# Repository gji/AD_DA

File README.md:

AD_DA
=====

AD/DA for Opal Kelly XEM6310

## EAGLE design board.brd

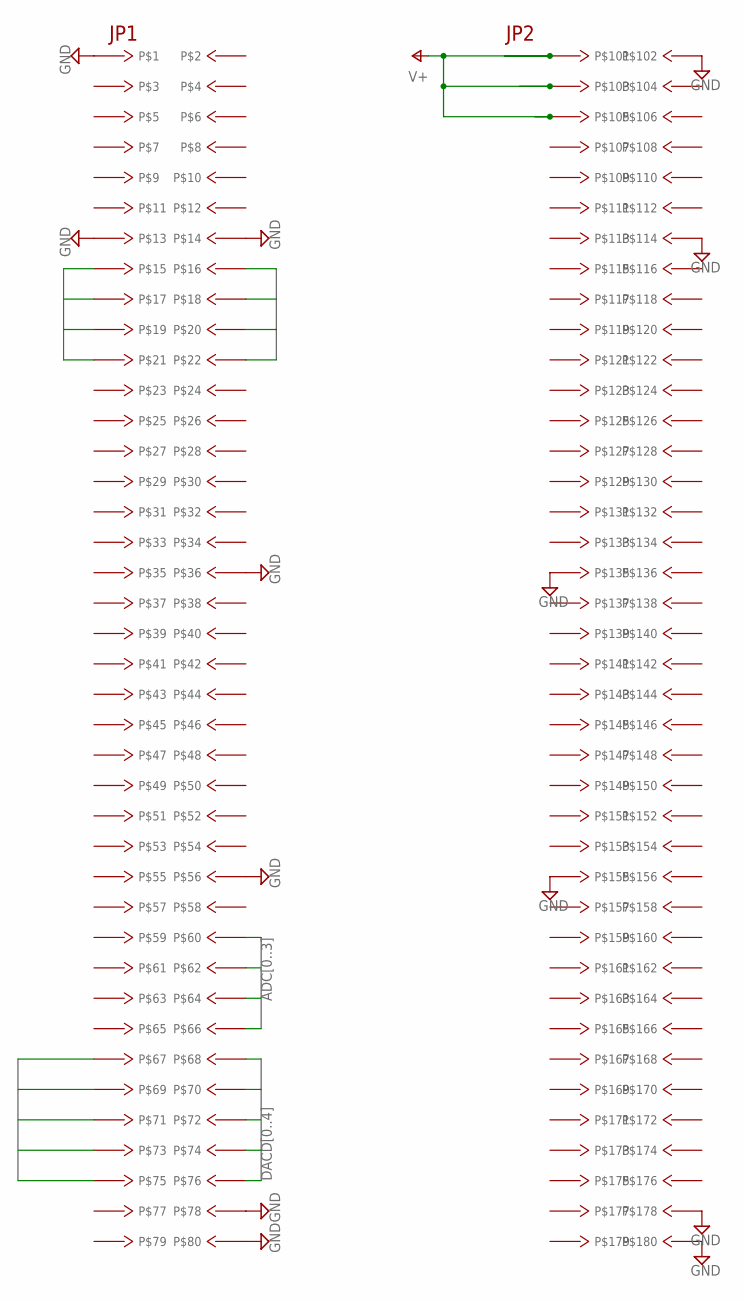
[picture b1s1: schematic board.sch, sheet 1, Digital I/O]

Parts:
J1: XEM6310

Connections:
ADC0: J1.266; also elsewhere on the board
ADC1: J1.264; also elsewhere on the board
ADC2: J1.262; also elsewhere on the board
ADC3: J1.260; also elsewhere on the board
ADC7: J1.222; also elsewhere on the board
ADC8: J1.220; also elsewhere on the board
ADC9: J1.218; also elsewhere on the board
ADC10: J1.216; also elsewhere on the board
ADC11: J1.221; also elsewhere on the board
ADC12: J1.219; also elsewhere on the board
ADC13: J1.217; also elsewhere on the board
ADC14: J1.215; also elsewhere on the board
DACD0: J1.268; also elsewhere on the board
DACD1: J1.270; also elsewhere on the board
DACD2: J1.272; also elsewhere on the board
DACD3: J1.274; also elsewhere on the board
DACD4: J1.276; also elsewhere on the board
DACD5: J1.267; also elsewhere on the board
DACD6: J1.269; also elsewhere on the board
DACD7: J1.271; also elsewhere on the board
DACD8: J1.273; also elsewhere on the board
DACD9: J1.275; also elsewhere on the board
GND: J1.102, J1.114, J1.135, J1.155, J1.178, J1.180, J1.201, J1.213, J1.214, J1.236, J1.256, J1.278, J1.280; also elsewhere on the board
V+: J1.101, J1.103, J1.105; also elsewhere on the board

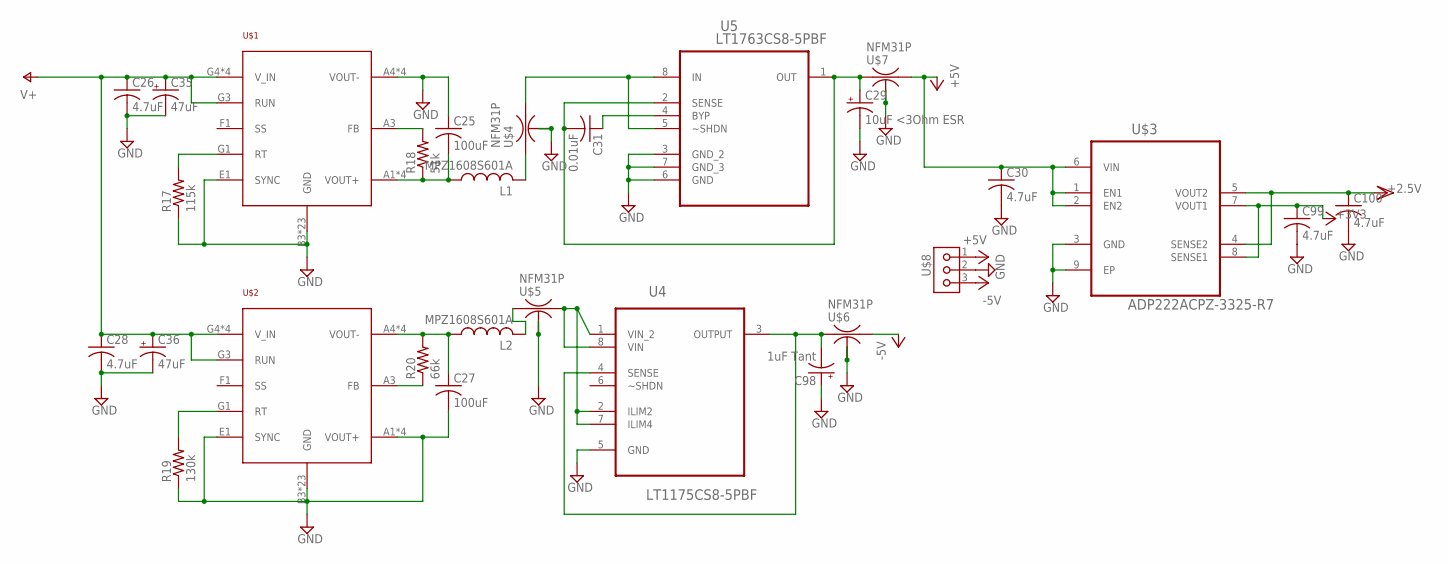
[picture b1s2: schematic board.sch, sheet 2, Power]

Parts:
C25, C27: 100uF; C1210
C26, C28, C30, C99, C100: 4.7uF; C0603
C29: 10uF <3Ohm ESR; C0603T
C31: 0.01uF; C0603
C35, C36: 47uF; UD-4X5,8_NICHICON
C98: 1uF Tant; C0603T
L1, L2: MPZ1608S601A; C0603
R17: 115k; R0603
R18: 51k; R0603
R19: 130k; R0603
R20: 66k; R0603
U4: LT1175CS8-5PBF; SOIC127P600X175-8N
U5: LT1763CS8-5PBF; SOIC127P600X175-8N
U$1, U$2: LTM8045; BGA-40
U$3: ADP222ACPZ-3325-R7; QFN50P200X200X60-9N
U$4, U$5, U$6, U$7: NFM31P
U$8: KK3V; KK-V-3

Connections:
+3V3: C99.1, U$3.7 (VOUT1), U$3.8 (SENSE1); also elsewhere on the board
+5V: C30.1, U$3.1 (EN1), U$3.2 (EN2), U$3.6 (VIN), U$7.OUT (3), U$8.1; also elsewhere on the board
-5V: U$6.OUT (3), U$8.3; also elsewhere on the board
GND: C25.1, C26.2, C27.2, C28.2, C29.-, C30.2, C35.-, C36.-, C98.+, C99.2, C100.2, R17.1, R19.1, U4.5 (GND), U5.3 (GND_2), U5.6 (GND), U5.7 (GND_3), U$1.A4 (VOUT-), U$1.A5 (VOUT-), U$1.B3 (GND), U$1.B4 (VOUT-), U$1.B5 (VOUT-), U$1.C1 (GND), U$1.C2 (GND), U$1.C3 (GND), U$1.C4 (GND), U$1.C5 (GND), U$1.D1 (GND), U$1.D2 (GND), U$1.D3 (GND), U$1.D4 (GND), U$1.D5 (GND), U$1.E1 (SYNC), U$1.E2 (GND), U$1.E3 (GND), U$1.E4 (GND), U$1.E5 (GND), U$1.F2 (GND), U$1.F3 (GND), U$1.F4 (GND), U$1.F5 (GND), U$1.G2 (GND), U$1.H1 (GND), U$1.H2 (GND), U$1.H3 (GND), U$2.A1 (VOUT+), U$2.A2 (VOUT+), U$2.B1 (VOUT+), U$2.B2 (VOUT+), U$2.B3 (GND), U$2.C1 (GND), U$2.C2 (GND), U$2.C3 (GND), U$2.C4 (GND), U$2.C5 (GND), U$2.D1 (GND), U$2.D2 (GND), U$2.D3 (GND), U$2.D4 (GND), U$2.D5 (GND), U$2.E1 (SYNC), U$2.E2 (GND), U$2.E3 (GND), U$2.E4 (GND), U$2.E5 (GND), U$2.F2 (GND), U$2.F3 (GND), U$2.F4 (GND), U$2.F5 (GND), U$2.G2 (GND), U$2.H1 (GND), U$2.H2 (GND), U$2.H3 (GND), U$3.3 (GND), U$3.9 (EP), U$4.GND (2), U$4.GND2 (2), U$5.GND (2), U$5.GND2 (2), U$6.GND (2), U$6.GND2 (2), U$7.GND (2), U$7.GND2 (2), U$8.2; also elsewhere on the board
unnamed: L1.2, U$4.IN (1)
unnamed: R19.2, U$2.G1 (RT)
unnamed: R17.2, U$1.G1 (RT)
unnamed: R18.2, U$1.A3 (FB)
unnamed: C25.2, L1.1, R18.1, U$1.A1 (VOUT+), U$1.A2 (VOUT+), U$1.B1 (VOUT+), U$1.B2 (VOUT+)
unnamed: C27.1, L2.1, R20.2, U$2.A4 (VOUT-), U$2.A5 (VOUT-), U$2.B4 (VOUT-), U$2.B5 (VOUT-)
unnamed: R20.1, U$2.A3 (FB)
unnamed: L2.2, U$5.IN (1)
unnamed: U4.1 (VIN_2), U4.2 (ILIM2), U4.7 (ILIM4), U4.8 (VIN), U$5.OUT (3)
unnamed: C31.1, U5.4 (BYP)
unnamed: U5.5 (~SHDN), U5.8 (IN), U$4.OUT (3)
unnamed: C98.-, U4.3 (OUTPUT), U4.4 (SENSE), U$6.IN (1)
unnamed: C29.+, C31.2, U5.1 (OUT), U5.2 (SENSE), U$7.IN (1)
V+: C26.1, C28.1, C35.+, C36.+, U$1.G3 (RUN), U$1.G4 (V_IN), U$1.G5 (V_IN), U$1.H4 (V_IN), U$1.H5 (V_IN), U$2.G3 (RUN), U$2.G4 (V_IN), U$2.G5 (V_IN), U$2.H4 (V_IN), U$2.H5 (V_IN); also elsewhere on the board
VDD: C100.1, U$3.4 (SENSE2), U$3.5 (VOUT2); also elsewhere on the board

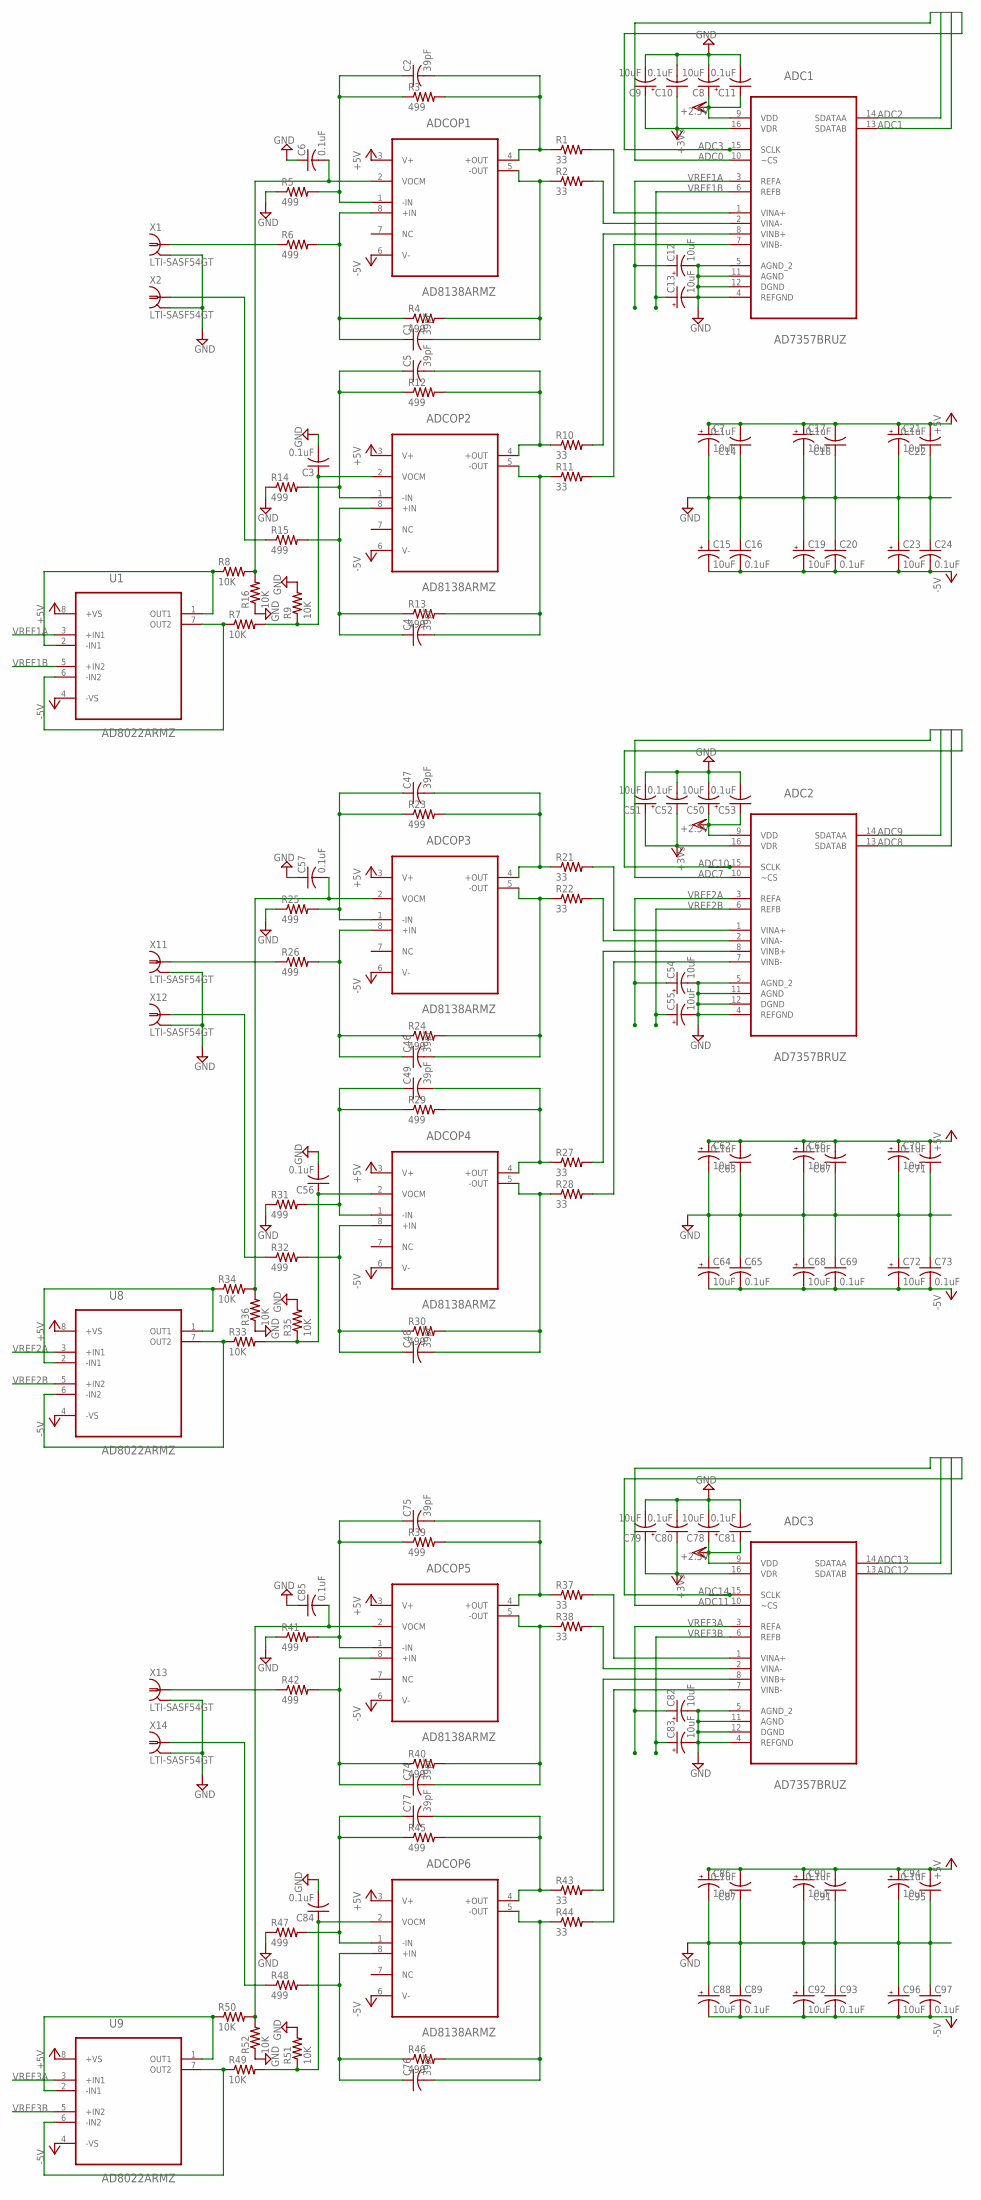
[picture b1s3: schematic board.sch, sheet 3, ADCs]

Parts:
ADC1, ADC2, ADC3: AD7357BRUZ; SOP65P640X120-16N
ADCOP1, ADCOP2, ADCOP3, ADCOP4, ADCOP5, ADCOP6: AD8138ARMZ; SOP65P490X110-8N
C1, C2, C4, C5, C46, C47, C48, C49, C74, C75, C76, C77: 39pF; C0603
C3, C6, C10, C11, C14, C16, C18, C20, C22, C24, C52, C53, C56, C57, C63, C65, C67, C69, C71, C73, C80, C81, C84, C85, C87, C89, C91, C93, C95, C97: 0.1uF; C0603
C7, C8, C9, C12, C13, C15, C17, C19, C21, C23, C50, C51, C54, C55, C62, C64, C66, C68, C70, C72, C78, C79, C82, C83, C86, C88, C90, C92, C94, C96: 10uF; C0603T
R1, R2, R10, R11, R21, R22, R27, R28, R37, R38, R43, R44: 33; R0603
R3, R4, R5, R6, R12, R13, R14, R15, R23, R24, R25, R26, R29, R30, R31, R32, R39, R40, R41, R42, R45, R46, R47, R48: 499; R0603
R7, R8, R9, R16, R33, R34, R35, R36, R49, R50, R51, R52: 10K; R0603
U1, U8, U9: AD8022ARMZ; SOP65P490X110-8N
X1, X2, X11, X12, X13, X14: LTI-SASF54GT

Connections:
+3V3: ADC1.16 (VDR), ADC2.16 (VDR), ADC3.16 (VDR), C9.+, C10.1, C51.+, C52.1, C79.+, C80.1; also elsewhere on the board
+5V: ADCOP1.3 (V+), ADCOP2.3 (V+), ADCOP3.3 (V+), ADCOP4.3 (V+), ADCOP5.3 (V+), ADCOP6.3 (V+), C7.+, C14.2, C17.+, C18.2, C21.+, C22.2, C62.+, C63.2, C66.+, C67.2, C70.+, C71.2, C86.+, C87.2, C90.+, C91.2, C94.+, C95.2, U1.8 (+VS), U8.8 (+VS), U9.8 (+VS); also elsewhere on the board
-5V: ADCOP1.6 (V-), ADCOP2.6 (V-), ADCOP3.6 (V-), ADCOP4.6 (V-), ADCOP5.6 (V-), ADCOP6.6 (V-), C15.-, C16.2, C19.-, C20.2, C23.-, C24.2, C64.-, C65.2, C68.-, C69.2, C72.-, C73.2, C88.-, C89.2, C92.-, C93.2, C96.-, C97.2, U1.4 (-VS), U8.4 (-VS), U9.4 (-VS); also elsewhere on the board
ADC0: ADC1.10 (~CS); also elsewhere on the board
ADC1: ADC1.13 (SDATAB); also elsewhere on the board
ADC2: ADC1.14 (SDATAA); also elsewhere on the board
ADC3: ADC1.15 (SCLK); also elsewhere on the board
ADC7: ADC2.10 (~CS); also elsewhere on the board
ADC8: ADC2.13 (SDATAB); also elsewhere on the board
ADC9: ADC2.14 (SDATAA); also elsewhere on the board
ADC10: ADC2.15 (SCLK); also elsewhere on the board
ADC11: ADC3.10 (~CS); also elsewhere on the board
ADC12: ADC3.13 (SDATAB); also elsewhere on the board
ADC13: ADC3.14 (SDATAA); also elsewhere on the board
ADC14: ADC3.15 (SCLK); also elsewhere on the board
GND: ADC1.4 (REFGND), ADC1.5 (AGND_2), ADC1.11 (AGND), ADC1.12 (DGND), ADC2.4 (REFGND), ADC2.5 (AGND_2), ADC2.11 (AGND), ADC2.12 (DGND), ADC3.4 (REFGND), ADC3.5 (AGND_2), ADC3.11 (AGND), ADC3.12 (DGND), C3.2, C6.1, C7.-, C8.-, C9.-, C10.2, C11.2, C12.-, C13.-, C14.1, C15.+, C16.1, C17.-, C18.1, C19.+, C20.1, C21.-, C22.1, C23.+, C24.1, C50.-, C51.-, C52.2, C53.2, C54.-, C55.-, C56.2, C57.1, C62.-, C63.1, C64.+, C65.1, C66.-, C67.1, C68.+, C69.1, C70.-, C71.1, C72.+, C73.1, C78.-, C79.-, C80.2, C81.2, C82.-, C83.-, C84.2, C85.1, C86.-, C87.1, C88.+, C89.1, C90.-, C91.1, C92.+, C93.1, C94.-, C95.1, C96.+, C97.1, R5.1, R9.2, R14.1, R16.1, R25.1, R31.1, R35.2, R36.1, R41.1, R47.1, R51.2, R52.1, X1.2, X1.3 (2), X1.4 (2), X1.5 (2), X2.2, X2.3 (2), X2.4 (2), X2.5 (2), X11.2, X11.3 (2), X11.4 (2), X11.5 (2), X12.2, X12.3 (2), X12.4 (2), X12.5 (2), X13.2, X13.3 (2), X13.4 (2), X13.5 (2), X14.2, X14.3 (2), X14.4 (2), X14.5 (2); also elsewhere on the board
unnamed: ADC1.8 (VINB+), R10.2
unnamed: ADCOP1.5 (-OUT), C1.2, R2.1, R4.2
unnamed: ADCOP1.1 (-IN), C2.1, R3.1, R5.2
unnamed: ADCOP1.8 (+IN), C1.1, R4.1, R6.2
unnamed: R7.1, U1.6 (-IN2), U1.7 (OUT2)
unnamed: R8.1, U1.1 (OUT1), U1.2 (-IN1)
unnamed: ADCOP1.2 (VOCM), C6.2, R8.2, R16.2
unnamed: ADC1.1 (VINA+), R1.2
unnamed: ADC1.2 (VINA-), R2.2
unnamed: ADCOP1.4 (+OUT), C2.2, R1.1, R3.2
unnamed: ADC1.7 (VINB-), R11.2
unnamed: ADCOP2.5 (-OUT), C4.2, R11.1, R13.2
unnamed: ADCOP2.1 (-IN), C5.1, R12.1, R14.2
unnamed: ADCOP2.8 (+IN), C4.1, R13.1, R15.2
unnamed: ADCOP2.2 (VOCM), C3.1, R7.2, R9.1
unnamed: ADCOP2.4 (+OUT), C5.2, R10.1, R12.2
unnamed: R15.1, X2.1
unnamed: R6.1, X1.1
unnamed: ADCOP3.5 (-OUT), C46.2, R22.1, R24.2
unnamed: ADCOP3.1 (-IN), C47.1, R23.1, R25.2
unnamed: ADCOP3.8 (+IN), C46.1, R24.1, R26.2
unnamed: ADC2.1 (VINA+), R21.2
unnamed: ADC2.2 (VINA-), R22.2
unnamed: ADCOP3.4 (+OUT), C47.2, R21.1, R23.2
unnamed: ADCOP4.5 (-OUT), C48.2, R28.1, R30.2
unnamed: ADCOP4.1 (-IN), C49.1, R29.1, R31.2
unnamed: ADCOP4.8 (+IN), C48.1, R30.1, R32.2
unnamed: ADCOP4.4 (+OUT), C49.2, R27.1, R29.2
unnamed: ADC2.8 (VINB+), R27.2
unnamed: ADC2.7 (VINB-), R28.2
unnamed: R32.1, X12.1
unnamed: R26.1, X11.1
unnamed: R33.1, U8.6 (-IN2), U8.7 (OUT2)
unnamed: R34.1, U8.1 (OUT1), U8.2 (-IN1)
unnamed: ADCOP3.2 (VOCM), C57.2, R34.2, R36.2
unnamed: ADCOP4.2 (VOCM), C56.1, R33.2, R35.1
unnamed: ADCOP5.5 (-OUT), C74.2, R38.1, R40.2
unnamed: ADCOP5.1 (-IN), C75.1, R39.1, R41.2
unnamed: ADCOP5.8 (+IN), C74.1, R40.1, R42.2
unnamed: ADC3.1 (VINA+), R37.2
unnamed: ADC3.2 (VINA-), R38.2
unnamed: ADCOP5.4 (+OUT), C75.2, R37.1, R39.2
unnamed: ADCOP6.5 (-OUT), C76.2, R44.1, R46.2
unnamed: ADCOP6.1 (-IN), C77.1, R45.1, R47.2
unnamed: ADCOP6.8 (+IN), C76.1, R46.1, R48.2
unnamed: ADCOP6.4 (+OUT), C77.2, R43.1, R45.2
unnamed: ADC3.8 (VINB+), R43.2
unnamed: ADC3.7 (VINB-), R44.2
unnamed: R48.1, X14.1
unnamed: R42.1, X13.1
unnamed: R49.1, U9.6 (-IN2), U9.7 (OUT2)
unnamed: R50.1, U9.1 (OUT1), U9.2 (-IN1)
unnamed: ADCOP5.2 (VOCM), C85.2, R50.2, R52.2
unnamed: ADCOP6.2 (VOCM), C84.1, R49.2, R51.1
VDD: ADC1.9 (VDD), ADC2.9 (VDD), ADC3.9 (VDD), C8.+, C11.1, C50.+, C53.1, C78.+, C81.1; also elsewhere on the board
VREF1A: ADC1.3 (REFA), C12.+, U1.3 (+IN1)
VREF1B: ADC1.6 (REFB), C13.+, U1.5 (+IN2)
VREF2A: ADC2.3 (REFA), C54.+, U8.3 (+IN1)
VREF2B: ADC2.6 (REFB), C55.+, U8.5 (+IN2)
VREF3A: ADC3.3 (REFA), C82.+, U9.3 (+IN1)
VREF3B: ADC3.6 (REFB), C83.+, U9.5 (+IN2)

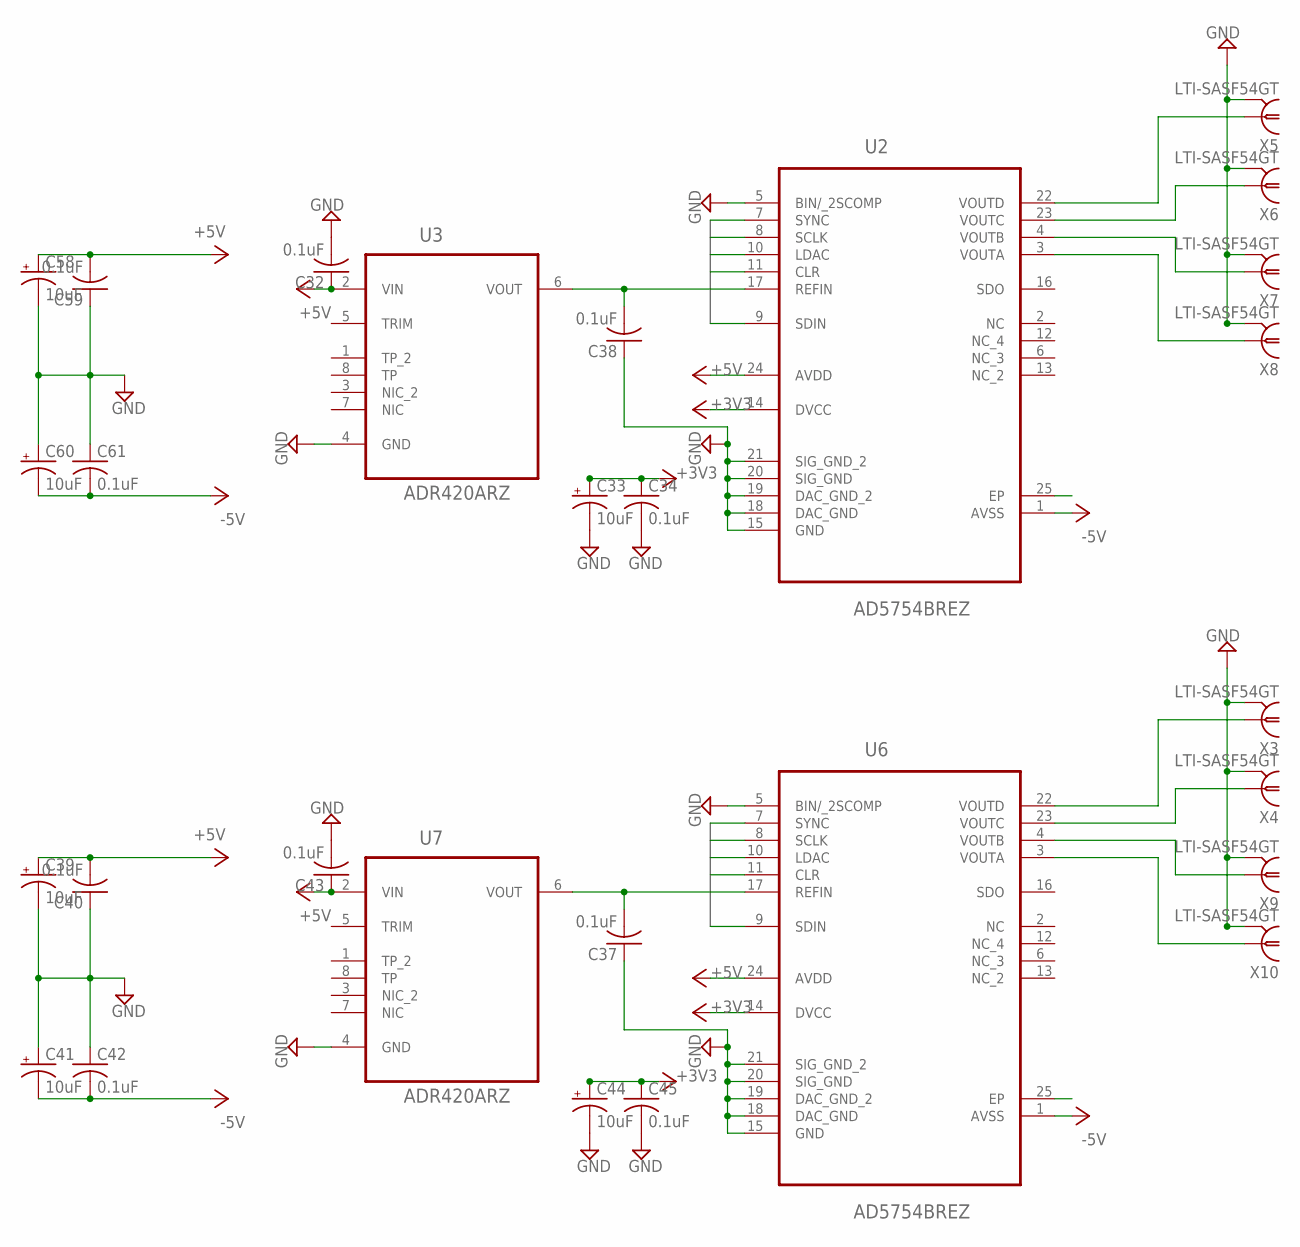
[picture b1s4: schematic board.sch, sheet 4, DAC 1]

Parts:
C32, C34, C37, C38, C40, C42, C43, C45, C59, C61: 0.1uF; C0603
C33, C39, C41, C44, C58, C60: 10uF; C0603T
U2, U6: AD5754BREZ; SOP65P640X120-25N
U3, U7: ADR420ARZ; SOIC127P600X175-8N
X3, X4, X5, X6, X7, X8, X9, X10: LTI-SASF54GT

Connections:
+3V3: C33.+, C34.1, C44.+, C45.1, U2.14 (DVCC), U6.14 (DVCC); also elsewhere on the board
+5V: C32.1, C39.+, C40.2, C43.1, C58.+, C59.2, U2.24 (AVDD), U3.2 (VIN), U6.24 (AVDD), U7.2 (VIN); also elsewhere on the board
-5V: C41.-, C42.2, C60.-, C61.2, U2.1 (AVSS), U6.1 (AVSS); also elsewhere on the board
DACD0: U2.7 (SYNC); also elsewhere on the board
DACD1: U2.8 (SCLK); also elsewhere on the board
DACD2: U2.9 (SDIN); also elsewhere on the board
DACD3: U2.10 (LDAC); also elsewhere on the board
DACD4: U2.11 (CLR); also elsewhere on the board
DACD5: U6.7 (SYNC); also elsewhere on the board
DACD6: U6.8 (SCLK); also elsewhere on the board
DACD7: U6.9 (SDIN); also elsewhere on the board
DACD8: U6.10 (LDAC); also elsewhere on the board
DACD9: U6.11 (CLR); also elsewhere on the board
GND: C32.2, C33.-, C34.2, C37.1, C38.1, C39.-, C40.1, C41.+, C42.1, C43.2, C44.-, C45.2, C58.-, C59.1, C60.+, C61.1, U2.5 (BIN/_2SCOMP), U2.15 (GND), U2.18 (DAC_GND), U2.19 (DAC_GND_2), U2.20 (SIG_GND), U2.21 (SIG_GND_2), U3.4 (GND), U6.5 (BIN/_2SCOMP), U6.15 (GND), U6.18 (DAC_GND), U6.19 (DAC_GND_2), U6.20 (SIG_GND), U6.21 (SIG_GND_2), U7.4 (GND), X3.2, X3.3 (2), X3.4 (2), X3.5 (2), X4.2, X4.3 (2), X4.4 (2), X4.5 (2), X5.2, X5.3 (2), X5.4 (2), X5.5 (2), X6.2, X6.3 (2), X6.4 (2), X6.5 (2), X7.2, X7.3 (2), X7.4 (2), X7.5 (2), X8.2, X8.3 (2), X8.4 (2), X8.5 (2), X9.2, X9.3 (2), X9.4 (2), X9.5 (2), X10.2, X10.3 (2), X10.4 (2), X10.5 (2); also elsewhere on the board
unnamed: U2.22 (VOUTD), X5.1
unnamed: U2.4 (VOUTB), X7.1
unnamed: U2.23 (VOUTC), X6.1
unnamed: U2.3 (VOUTA), X8.1
unnamed: C38.2, U2.17 (REFIN), U3.6 (VOUT)
unnamed: U6.22 (VOUTD), X3.1
unnamed: U6.4 (VOUTB), X9.1
unnamed: U6.23 (VOUTC), X4.1
unnamed: U6.3 (VOUTA), X10.1
unnamed: C37.2, U6.17 (REFIN), U7.6 (VOUT)

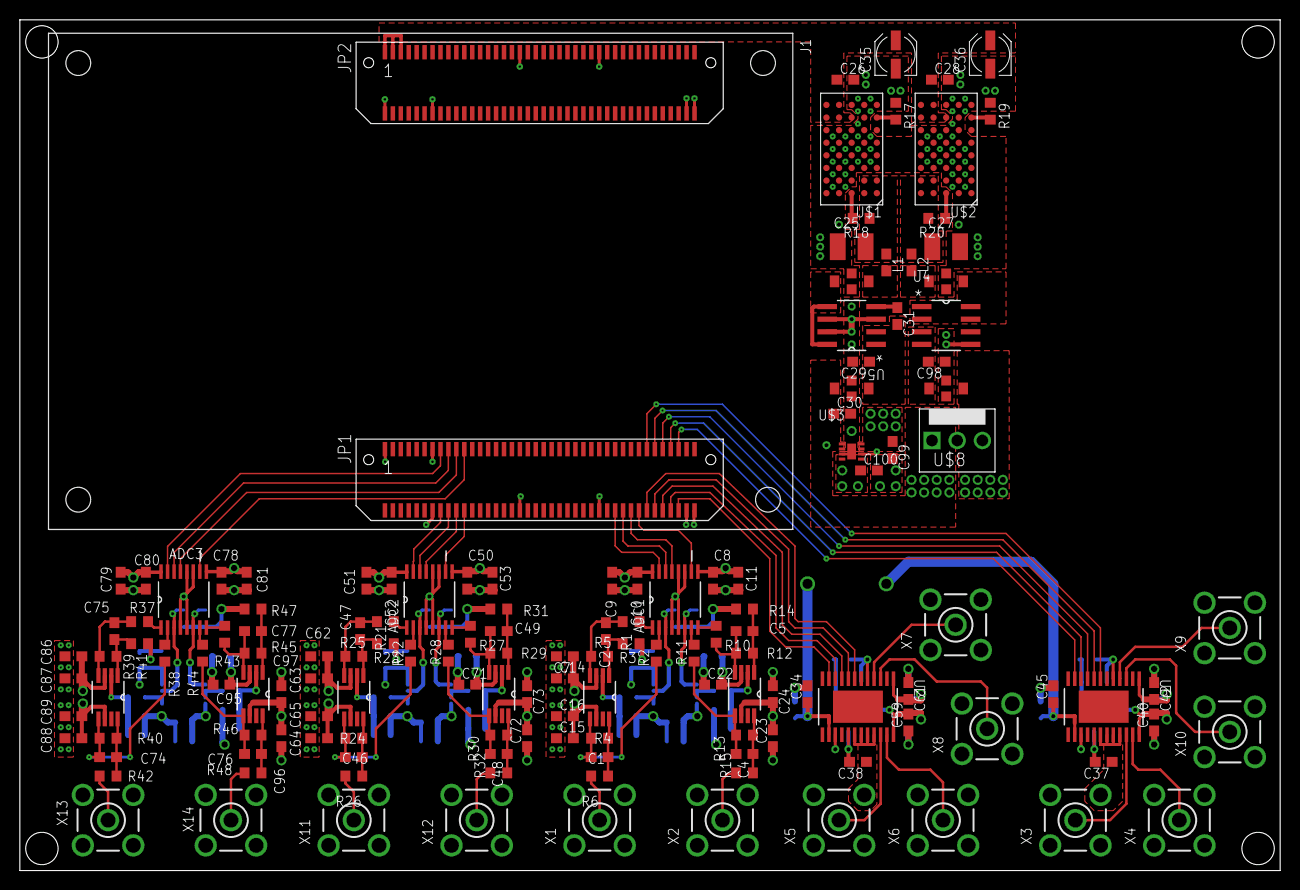
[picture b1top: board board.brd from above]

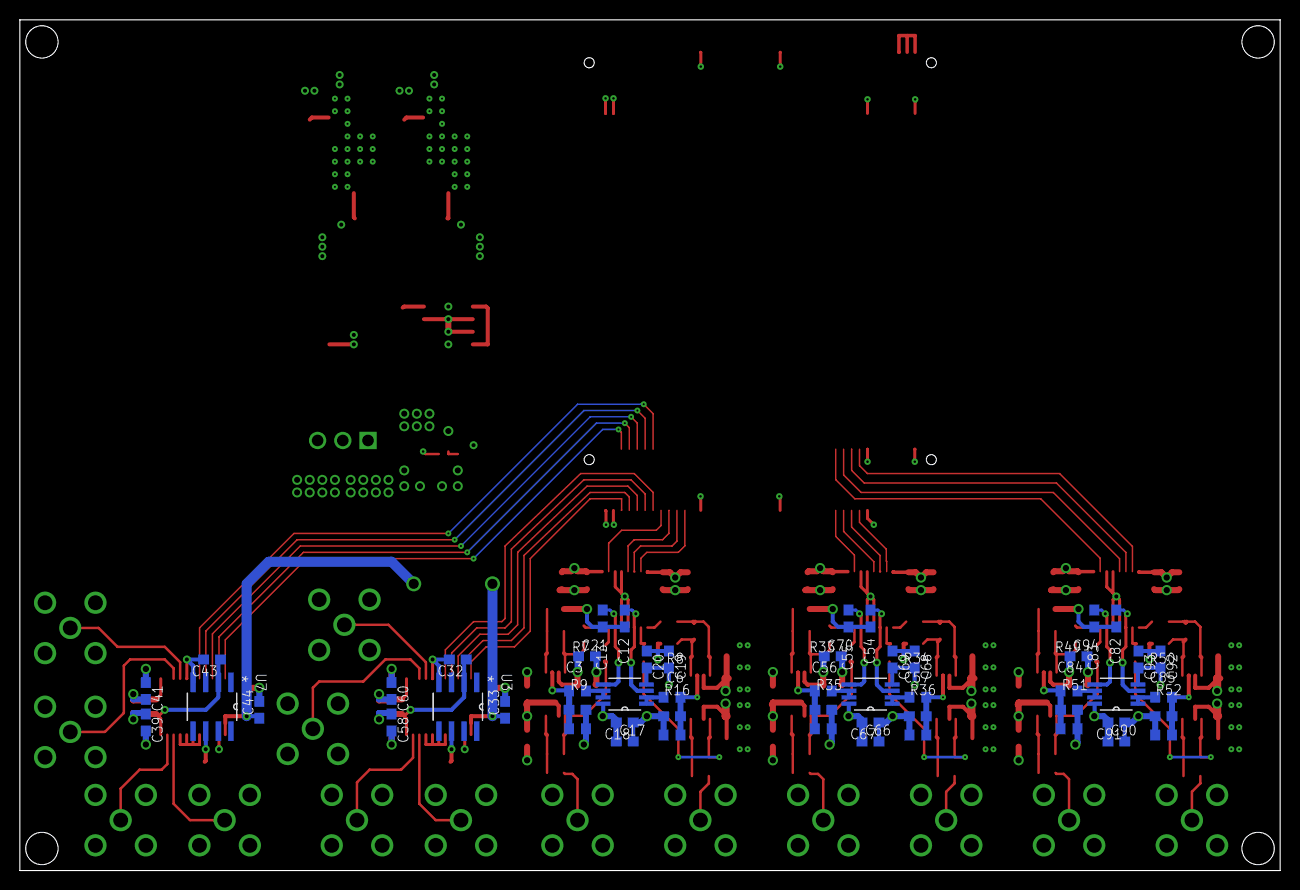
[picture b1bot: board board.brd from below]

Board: 4 copper layers, 127.0 x 85.7 mm, 195 parts (52 on the bottom side), 111 nets.

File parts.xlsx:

Line | Qty | Value | Device | Package | Parts | Description | MPN | Digikey | Qty | Notes
1 | 1 | 0.01uF | C-USC0603 | C0603 | C31 | CAPACITOR, American symbol |  | 445-2664-1-ND | 1
2 | 40 | 0.1uF | C-USC0603 | C0603 | C3, C6, C10, C11, C14, C16, C18, C20, C22, C24, C32, C34, C37, C38, C40, C42, C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 | CAPACITOR, American symbol |  | 445-6984-1-ND | 40 | Probably can find cheaper
3 | 2 | 100uF | C-USC1210 | C1210 | C25, C27 | CAPACITOR, American symbol |  | 445-11840-1-ND | 2
4 | 2 | 100uF | CPOL-USUD-4X5,8 | UD-4X5,8_NICHICON | C35, C36 | POLARIZED CAPACITOR, American symbol |  | P15090CT-ND | 2
5 | 12 | 10K | R-US_R0603 | R0603 | R7, R8, R9, R16, R33, R34, R35, R36, R49, R50, R51, R52 | RESISTOR, American symbol |  | RG16N10.0KWCT-ND | 12
6 | 36 | 10uF | CPOL-US | C0603T | C7, C8, C9, C12, C13, C15, C17, C19, C21, C23, C33, C39, C41, C44, C50, C51, C5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 | POLARIZED CAPACITOR, American symbol |  | 445­11238­1­ND | 36
7 | 1 | 10uF <3Ohm ESR | CPOL-US | C0603T | C29 | POLARIZED CAPACITOR, American symbol |  | 718-1673-1-ND | 1
8 | 1 | 115k | R-US_R0603 | R0603 | R17 | RESISTOR, American symbol |  | P115KDBCT-ND | 1
9 | 1 | 130k | R-US_R0603 | R0603 | R19 | RESISTOR, American symbol |  | P130KDBCT-ND | 1
10 | 1 | 1uF Tant | CPOL-US | C0603T | C98 | POLARIZED CAPACITOR, American symbol |  | 478-5352-1-ND | 1
11 | 12 | 33 | R-US_R0603 | R0603 | R1, R2, R10, R11, R21, R22, R27, R28, R37, R38, R43, R44 | RESISTOR, American symbol |  | A103087CT-ND | 12
12 | 12 | 39pF | C-USC0603 | C0603 | C1, C2, C4, C5, C46, C47, C48, C49, C74, C75, C76, C77 | CAPACITOR, American symbol |  | 1276-2280-1-ND | 12
13 | 5 | 4.7uF | C-USC0603 | C0603 | C26, C28, C30, C99, C100 | CAPACITOR, American symbol |  | 1276-1282-1-ND | 5
14 | 24 | 499 | R-US_R0603 | R0603 | R3, R4, R5, R6, R12, R13, R14, R15, R23, R24, R25, R26, R29, R30, R31, R32, R39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 | RESISTOR, American symbol |  | P499DBCT-ND | 24 | Needs fairly high precision
15 | 1 | 51k | R-US_R0603 | R0603 | R18 | RESISTOR, American symbol |  | P51KDBCT-ND | 1
16 | 1 | 66k | R-US_R0603 | R0603 | R20 | RESISTOR, American symbol |  | P66.5KDBCT-ND | 1
17 | 2 | AD5754BREZ | AD5754BREZ | SOP65P640X120-25N | U2, U6 | IC, DAC, 16BIT, 100KSPS | AD5754BREZ | AD5754BREZ-ND | 2
18 | 3 | AD7357BRUZ | AD7357BRUZ | SOP65P640X120-16N | ADC1, ADC2, ADC3 | Differential Input, Dual, Simultaneous Sampling, 4.2 MSPS, 14-Bit, SAR ADC | AD7357BRUZ | AD7357WYRUZ-ND | 3
19 | 3 | AD8022ARMZ | AD8022ARMZ | SOP65P490X110-8N | U1, U8, U9 | Dual High Speed,Low Noise Op Amp | AD8022ARMZ | AD8022ARMZ-ND | 3
20 | 6 | AD8138ARMZ | AD8138ARMZ | SOP65P490X110-8N | ADCOP1, ADCOP2, ADCOP3, ADCOP4, ADCOP5, ADCOP6 | Low Distortion Differential ADC Driver | AD8138ARMZ | AD8138ARMZ-ND | 6
21 | 1 | ADP222ACPZ-3325-R7 | ADP222ACPZ-3325-R7 | QFN50P200X200X60-9N | U$3 |  |  | ADP222ACPZ-3325-R7CT-ND | 1
22 | 2 | ADR420ARZ | ADR420ARZ | SOIC127P600X175-8N | U3, U7 | Ultraprecision, Low Noise, 2.048 V/2.500 V/ 3.00 V/5.00 V XFET® Voltage Referen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 | ADR420ARZ | ADR420ARZ-ND | 2
23 | 1 | KK3V | KK3V | KK-V-3 | U$8 | Molex KK |  |  | 1
24 | 1 | LT1175CS8-5PBF | LT1175CS8-5PBF | SOIC127P600X175-8N | U4 | 500mA Negative Low Dropout Micropower Regulator | LT1175CS8-5#PBF | LT1175CS8-5#PBF-ND | 1
25 | 1 | LT1763CS8-5PBF | LT1763CS8-5PBF | SOIC127P600X175-8N | U5 | 500mA, Low Noise, LDO Micropower Regulators | LT1763CS8-5#PBF | LT1763CS8-5#PBF-ND | 1
26 | 14 | LTI-SASF54GT | LTI-SASF54GT | LTI-SASF54GT | X1, X2, X3, X4, X5, X6, X7, X8, X9, X10, X11, X12, X13, X14 | SMA vertical PCB thrue hole jack |  |  | 14
27 | 2 | LTM8045 | LTM8045 | BGA-40 | U$1, U$2 |  |  | LTM8045EY#PBF-ND | 2
28 | 2 | MPZ1608S601A | L-US | C0603 | L1, L2 | INDUCTOR, American symbol |  | 445-2205-1-ND | 2
29 | 4 | NFM31P | NFM31P | NFM31P | U$4, U$5, U$6, U$7 |  |  | 490-6984-1-ND | 4
30 | 1 | XEM6310 | XEM6310 | XEM6310 | J1 |  |  |  | 1
31

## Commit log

2013-10-09 Layout changes
2013-10-09 Back to latest revision
2013-10-09 Small Changes
    Trace width modification, minor layout changes of ADC reference voltage
    caps, ground plane now not split.
2013-10-10 Fixed ground plane line
2013-10-11 More changes
2013-10-11 Finished power to board
2013-10-25 Bug fix
    Fixed strange bug with board unable to open
2013-10-25 Copied AD/DA devices.
    Schematic needs to be fixed for consistency.
2013-10-29 Board/schematic consistency
    Need input wiring now
2013-10-30 Routed signals
    Need to fix SMA connector spacing
2013-10-31 Added .gitignore
2013-10-31 Edited .gitignore
    Now ignores backups
2013-10-31 Deleted unnecessary backups
2013-10-31 Fixed power
    Added caps for all linear regulators
2013-10-31 Finalized
    Finished and ordered
2013-11-01 Solder paste gerbers
    Calculated paste gerbers
2014-04-16 Added parts xlsx
2014-05-01 added some helpful pdfs
